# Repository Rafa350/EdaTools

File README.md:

# EdaTools

Tools and utilities for PCB design.
!!!Very early version. Runs ok for my works.

## EdaImport
* Convert EAGLE v7 BRD file to EdaTools board file (.XBRD)
* Convert EAGLE v7 LBR file to EdaTools library file (.XLIB)
* Convert KiCad pcb file to EdaTools board file (.XBRD)

## EdaExport
* Convert EdaTools board file (.XBRD) to EAGLE or KiCAD
* Convert EdaTools library file (.XLIB) to KiCAD footprint library

## EdaExtractor.
* Extract information from board (BOM, Centroids, etc)

## EdaPanelizer.
* Merge any number of boards to create a single board panel.

## EdaCAMTool.
* Create production files from CAM project file (.XCAM).
* Generate gerber X3 image files.
* Generate gerber X3 drill and route files.
* Generate IPC-D356 file.
* Generate IPC-2581C file.
* Compliant with Ucamco Gerber File Format Specification (www.ucamco.com).
* Passed Gerber test with "https://gerber-viewer.ucamco.com/".
* Passed IPC2581C test with 3D PCBA Viewer.

## Notes.
* I used this tool for convert KiCAD to IPC2581 for board fabrication. Pending for assembly.

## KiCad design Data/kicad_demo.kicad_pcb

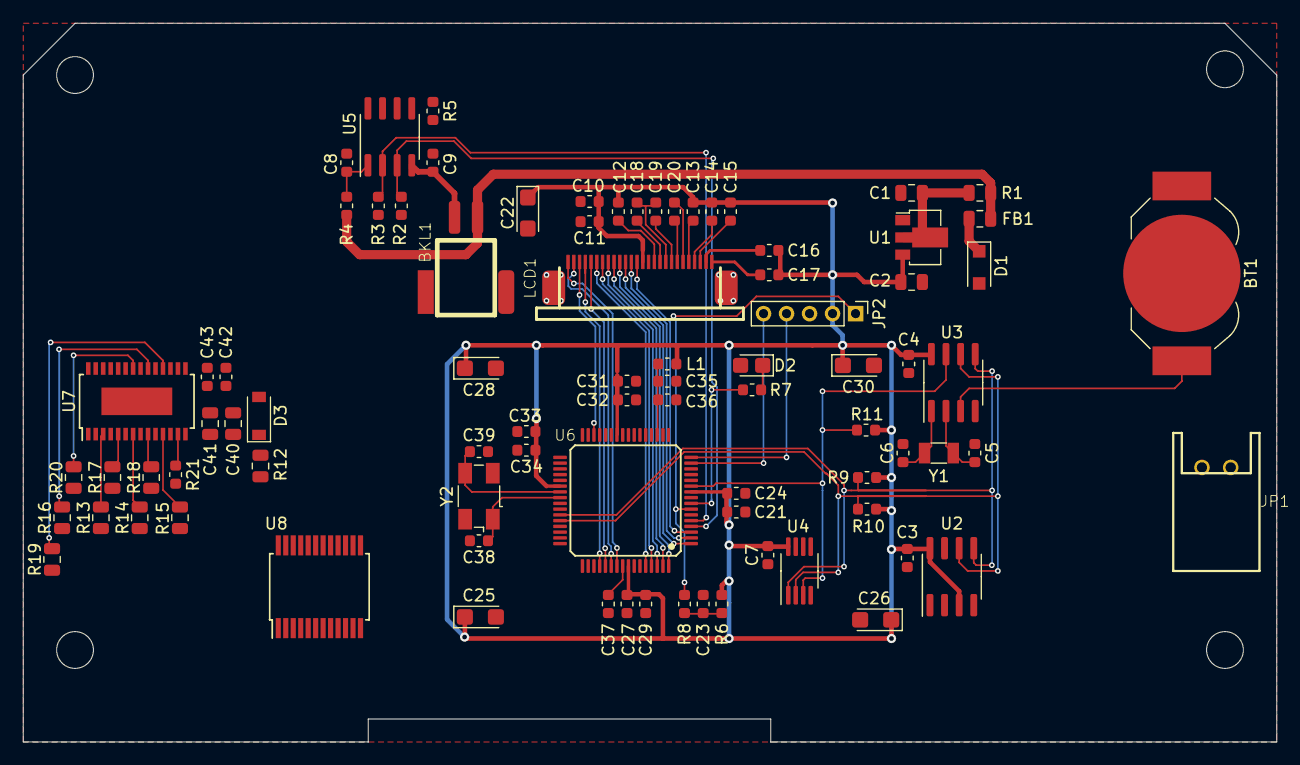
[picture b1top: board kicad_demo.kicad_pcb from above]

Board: 2 copper layers, 109.0 x 62.5 mm, 84 parts (0 on the bottom side), 63 nets.

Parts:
BKL1: ERC12864-3-BK; ER-CON2.0-2P-SMD
BT1: Battery_Cell; BatteryHolder_LINX_BAT-HLD-012-SMT
C1, C2: 4u7; C_0805_2012Metric
C3, C4, C7, C8, C10, C23, C24, C29, C32, C34, C36, C42: 100n; C_0603_1608Metric
C5, C6: 14p; C_0603_1608Metric
C9: 470n; C_0603_1608Metric
C11: 10u; C_0603_1608Metric
C12, C13, C14, C15, C16, C17, C18, C19, C20: 1u; C_0603_1608Metric
C21, C27, C31, C33, C35, C37: 10n; C_0603_1608Metric
C22, C25, C26, C28, C30: 10u; CP_EIA-3216-18_Kemet-A
C38, C39: 22p; C_0603_1608Metric
C40: 10u; C_0805_2012Metric
C41: 100n; C_0805_2012Metric
C43: 4u7; C_0603_1608Metric
D1: MBR0540; D_SOD-123F
D2: HSMG-C170; LED_0805_2012Metric_Castellated
D3: MMSZ5258BT1G; D_SOD-123
FB1: 600R; L_0805_2012Metric
JP1: S02B-XASK-1
JP2: PINHD-1X5-2MM; PinHeader_1x05_P2.00mm_Vertical
L1: 600R; L_0603_1608Metric
LCD1: ERC12864-3; ER-CON26HB-1
R1: 5R1; R_0805_2012Metric
R2, R3: 100K; R_0603_1608Metric
R4: 100R; R_0603_1608Metric
R5: 1K66; R_0603_1608Metric
R6, R11: 10K; R_0603_1608Metric
R7: 270; R_0603_1608Metric
R8: 1K; R_0603_1608Metric
R9, R10: 1K5; R_0603_1608Metric
R12: 150R; R_0805_2012Metric
R13, R14, R15, R16, R17, R18, R19, R20: 2K2; R_0805_2012Metric
R21: 15K; R_0603_1608Metric
U1: MCP1703A-3302_SOT89; SOT-89-3
U2: 24LC1025; SOIC-8_3.9x4.9mm_P1.27mm
U3: MCP7940N-xST; SOIC-8_3.9x4.9mm_P1.27mm
U4: MCP9804_MSOP; MSOP-8_3x3mm_P0.65mm
U5: STCS05; SOIC-8_3.9x4.9mm_P1.27mm
U6: PIC32MX4H_PT; TQFP64-10X10
U7: MAX31911; TSSOP-28-1EP_4.4x9.7mm_P0.65mm
U8: NCV7240; SSOP-24_5.3x8.2mm_P0.65mm
Y1: CM7V-T1A; Crystal_SMD_3215-2Pin_3.2x1.5mm
Y2: ABM3B; Crystal_SMD_Abracon_ABM3B-4Pin_5.0x3.2mm

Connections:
+3V3: C2.1, C3.1, C4.1, C7.1, C10.1, C11.1, C12.1, C13.1, C14.1, C15.1, C16.1, C17.1, C21.1, C22.1, C24.1, C25.1, C26.1, C27.1, C28.1, C29.1, C30.1, C31.1, C32.1, C33.1, C34.1, JP2.2, L1.2, LCD1.14, R6.1, R9.1, R10.1, R11.2, U1.3, U2.3, U2.8, U3.8, U4.8, U6.10, U6.26, U6.38, U6.57
+5V: BKL1.1, FB1.1, R1.2, R4.2
/CPU/LED: R7.1, U6.8
/CPU/MCLR: JP2.1, R8.2, U6.7
/CPU/PGEC1: JP2.5, U6.15
/CPU/PGED1: JP2.4, U6.16
ALERT: R11.1, U3.7, U4.3, U6.11
BK-EN: R2.1, U5.3, U6.4
BK-PWM: R3.1, U5.2, U6.5
DSP-A0: LCD1.3, U6.30
DSP-CS: LCD1.1, U6.55
DSP-D0: LCD1.6, U6.60
DSP-D1: LCD1.7, U6.61
DSP-D2: LCD1.8, U6.62
DSP-D3: LCD1.9, U6.63
DSP-D4: LCD1.10, U6.64
DSP-D5: LCD1.11, U6.1
DSP-D6: LCD1.12, U6.2
DSP-D7: LCD1.13, U6.3
DSP-RD: LCD1.5, U6.53
DSP-RST: LCD1.2, U6.54
DSP-WR: LCD1.4, U6.52
GND: BT1.2, C1.2, C2.2, C3.2, C4.2, C5.2, C6.2, C7.2, C8.2, C9.2, C10.2, C11.2, C21.2, C22.2, C23.1, C24.2, C25.2, C26.2, C27.2, C28.2, C29.2, C30.2, C31.2, C32.2, C33.2, C34.2, C35.2, C36.2, C37.2, C38.2, C39.2, D2.2, JP1.2, JP2.3, LCD1.15, R2.2, R3.2, R5.2, U1.1, U2.1, U2.2, U2.4, U2.7, U3.4, U4.4, U4.5, U4.6, U4.7, U5.6, U6.9, U6.20, U6.25, U6.41, Y2.2, Y2.4
GND1: C40.2, C41.2, C42.2, C43.2, D3.2, R21.2, U7.4, U7.6, U7.8, U7.10, U7.12, U7.17, U7.19, U7.21, U7.26, U7.27, U7.291, U7.292, U7.293, U7.294, U7.295, U7.296, U7.297, U7.298, U8.1, U8.2, U8.11, U8.12, U8.14, U8.15, U8.16, U8.17, U8.18
unnamed: BKL1.2, C9.1, U5.4
unnamed: BT1.11, BT1.12, U3.3
unnamed: C1.1, R1.1, U1.2
unnamed: C5.1, U3.2, Y1.1
unnamed: C6.1, U3.1, Y1.2
unnamed: C8.1, R4.1, U5.1
unnamed: C12.2, LCD1.16
unnamed: C13.2, LCD1.22
unnamed: C14.2, LCD1.23
unnamed: C15.2, LCD1.24
unnamed: C16.2, LCD1.25
unnamed: C17.2, LCD1.26
unnamed: C18.1, C19.1, LCD1.18
unnamed: C18.2, LCD1.17
unnamed: C19.2, LCD1.19
unnamed: C20.1, LCD1.21
unnamed: C20.2, LCD1.20
unnamed: C23.2, R6.2, R8.1
unnamed: C35.1, C36.1, L1.1, U6.19
unnamed: C37.1, U6.56
unnamed: C38.1, U6.40, Y2.1
unnamed: C39.1, U6.39, Y2.3
unnamed: C40.1, C41.1, D3.1, R12.1, U7.14
unnamed: C42.1, C43.1, U7.1, U7.2, U7.15, U8.13, U8.21, U8.24
unnamed: D1.1, FB1.2
unnamed: D1.2, JP1.1
unnamed: D2.1, R7.2
unnamed: R5.1, U5.5
unnamed: R13.1, U7.3
unnamed: R14.1, U7.7
unnamed: R15.1, U7.11
unnamed: R16.1, U7.20
unnamed: R17.1, U7.5
unnamed: R18.1, U7.9
unnamed: R19.1, U7.18
unnamed: R20.1, U7.22
unnamed: R21.1, U7.13
SCL1: R10.2, U2.6, U3.6, U4.2, U6.44
SDA1: R9.2, U2.5, U3.5, U4.1, U6.43

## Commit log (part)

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2018-01-26 Dibuix correcte de poligons en pantalla. Dibuix correcta de rectangles i cercles plens o perfilats Proves amb fons Hershey
2018-01-27 Millores en el gerber per acostar-se al maxim a les especificacions de ucamco Afeigit el parametre BoardSide en la generacio dels poligons
2018-01-27 Renombrada la llibraria CAM Eina CAM per la generacio de gerbers
2018-01-29 Millores en la lectura i escriptura de la placa en un stream
2018-01-29 Commit final del dia
2018-01-31 Afeigit attributs en el bloc Lectura dles atributs al carregar la placa. Eliminada la propietat isolation en les regions. Optimitzacio del generador gerber.
2018-01-31 Revisio dels visitadors Optimitzacio de la generacio dels fitxers gerbers
2018-02-01 Afeigits el readme i la llivcencia per github
2018-02-02 Millores en la deteccio d'errors de parametres en el generador gerber. Modificat la funcio d'escriure atributs gerber. Canvis en noms incongruents.
2018-02-03 Millores en el generador de visuals. Un visual per capa. Cada visual de capa te visuals fills dels elements de la capa. D'aquesta manera es pot controlar la transparencia, el color i la visibilitat d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
2018-02-04 Clase Angle per representar tots els angles de rotacio, arcs, etc El gerber ya representa correctament la separacio del perfil en els poligons
2018-02-06 Modificacions en el visor de plaques
2018-02-07 Implementacio dels fonts heshey Afeigit clearance en les senyals
2018-02-08 Creacio del font standard
2018-02-19 Gestio de fonst vectorials
2018-02-20 Fonts vectorials
2018-02-21 Creacio de fonts. El element text te en compte la rotacio i posicio de l'atribut
2018-02-22 Mes fonts Ajust de l'orientacio dels texts, tant literals, com asignats a un atribut.
2018-02-26 Optimitzacio llistes de poligons
2018-02-27 Reorganitzacio del projecte EdaImport
2018-02-27 Aliniacio textes
2018-02-28 Atributs de Part. Posicio rotacio i aliniacio. Nova clase TextDrawer per dibuixar textes. Es por derivar per dibuixar en qualsevol dispositiu vectorial
2018-03-02 Gestio dels parasmetres dels parts
2018-03-04 Poligons i fonts implementats amb arrays. PolygonBuilder adaptat a arrays de punts. Restructuracio de la carpeta Geometry.
2018-03-06 Creacio de les clases PointInt, SizeInt, i RectInt GlyphPoint es substutuit per PointInt
2018-03-07 Canvi de geometria double a int
2018-03-09 Canvi a aritmetica amb enters
2018-03-10 Complert el traspas a geometria amb enters
2018-03-11 final del dia
2018-03-14 Nou: Generacio de fitxers IPCD365
2018-03-14 Correccio de bugs en el calcul de la corona en vias i pads Millores el la generacio IPCD365
2018-03-15 Nova clase SignalVisitor
2018-03-17 Corregit errors amb arcs de mes de 180 graus
2018-03-21 Fitxers XSL per conversio a fitxers de produccio
2018-03-22 Reorganitzacio del projecte. Nova llibreria EdaCommonLibrary
2018-03-26 Commit de seguretat
2018-04-08 Fix: Peta quant intenta visualitzar una capa inexistent
2018-04-15 Carrega els fonts de la carpeta relativa al executable. Batch de generacio dels fitxers de produccio. Ignora les carpetes els fitxers de produccio (Data/Production/*)
2018-07-20 Millores en la deteccio d'error del importador eagle
2018-07-24 Implementacio GetOutline per l'element regio.
2018-07-25 Millores en la generacio de gerber Correccio en el el generador xsl del bom per eurocircuits
2018-07-26 Arreglos en CircleElement, RectangleElement Reorganitzacio de XmlNodeHelper
2018-07-30 Opcio Filled en objectes rectangle, circle i RegionElement Visuals per cada tipus d'objecte Pbjecte cachePen i cacheBrush com entitats separades
2018-07-30 Visuals de cada element
2018-07-31 Restructuracio del visor de plaques Zoom i pan correctes
2018-07-31 Millores generals en EdaPCBViewer Calcul del tamany de la placa. Bounding box de les linies. Metodes utils en PointInt, SizeInt i RectInt
2018-08-02 Arreglos cosmetics
2018-08-02 Optimitzacio zoom i pan en EdaPCBViewer
2018-08-06 Gnenerador CAM per fitxers DXS del perfil de la placa
2018-08-07 VisualDrawer optimitzat e independitzat de la resta.
2018-08-10 Nou lector de plaques. Gestio dels pads en els blocs millorada. Creacio retardade de les llistes d'atributs i pads
2018-08-12 Restructuracio Geometry Millores en la importacio Eagle Optimitzacio en XmlBoardReader i XmlBoardWriter Arreglos cosmetics generals
2018-08-13 Restructuracio dels fitxers i carpetes. Clases XmlWriterAdapter i XmlReaderAdapter. Cleses helper per Xml en cada tipus que ho necesiti. Mes lletres en els fonmts Nova clase DistanceUnits Nova clase 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
2018-08-27 Generacio de fitxers CAM per panells multiplaca
2018-08-28 Restructuracio del model
2018-08-29 Panelitzacio en la sortida gerber Lecturs de panells XPNL
2018-08-30 Generador CAM per ipc-d356 per panell
2018-09-07 Restructuracio de la gestio de capes. Cada element de la placa te el seu LayerSet on constant en quines capes el renderitzen. Si la placa en la que esta te una capa del LayerSet, la dibuixa, si no, c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
2018-09-07 Restructuracio general. Funcio Clone en elements de placa. Funcions d'extensio en XmlReaderAdapter pels tipus basics (Point, Size, Angle, etc
2018-09-08 Millores en el panelitzador. Gestio de les capes amb LayerId, i LayerSet Gestio de la capa outlineLayer
2018-09-09 Millores en el panelitzador. Revisio Block canvi de HashSet per List
2018-09-10 Implementacio amb noves col·leccions
2018-09-10 Proves amb WriteableBitmap
2018-09-11 Restructuracio dels fitxers board
2018-09-11 Millores en les coleccions per evitar memory leaks
2018-09-12 Revisio coleccions
2018-09-15 Restructuracio del render WPF
2018-09-16 Caper visuals (En estudi)
2018-09-19 Restructuracio en lectura i escriptura de fitxers XBRD
2018-09-20 Restructuracio
2018-09-27 Optimitzacione en el renderitzat
2018-10-20 Cambis cosmetics
2018-11-01 Millores en la carrega del projecte XCAM
2018-11-02 Millores en el generador CAM
2018-11-06 Millores en el procesador CAM
2018-11-16 Millores en la lectura dels fitxers de placa
2018-11-16 Corregit: No troba el schema per la lectura del fitxer XPNL
2018-11-19 Millores en la lectura de fitxers XPNL, XBRD i XCAM Hole nomes en la capa Hole, implicitament afecta a totes. Lectura de posicio i rotacio en projectes CAM
2018-11-21 Canvis en el format del fitxer xpnl
2018-11-23 Nou projecte EdaHDCLibrary
2018-11-25 Compilador HDL
2018-11-27 Millores en el parser HDL
2018-11-28 Gramatica pel HDL
2018-11-29 Parser PHDL completat Objectes AST complert
2018-11-29 Afeigit TODO
2018-11-30 Restructuracio de EdaPCBLibrary
2018-12-01 Restructuracio del model. Simplicifacio de les coleccions.
2018-12-02 Restructuracio i simplificacio
2018-12-04 Millores en el panelitzador
2018-12-04 Panelitzador
2018-12-06 Millores en el panelitzador.
2018-12-08 Correccio error greu en LayerSet.Parse que impedia la identificacio corerecte de les capes Correccio en la posicio del forats en els fitxers gerber
2018-12-09 Millores en el parser de LayerId
2018-12-10 Restructuracio en la llibraria EdaCAM
2018-12-11 Parametres d'entrada al panelitzador. Millores en el build
2018-12-13 Restructuracio i millores en l'editor de panells
2018-12-15 Restructuracio dels visitadors
2018-12-17 Restructuracio de BoardEditor Objectes visuals per BoardEditor
2018-12-21 Restructuracio dels editors Nou ensamblat per grafics wpf
2018-12-21 Mapa de conectivitat inici de la implementacio
2018-12-22 Restructuracio del editor de panells Simplificacio del renderitzat
2018-12-31 Canvi del format dels fitxert xpnl Correccio d'errors en el panelitzador i en el editor de panells
2018-12-31 Actualitzacio projecte doxygen
2019-01-05 Correccio del renderitzat de poligons en parts situats en la capa inferior
2019-01-07 Millores en VisualLayer
2019-01-09 Millores en EdaPanelizer Correccio d'errors en Setup
2019-01-09 Canvi en la forma d'identificar si un part esta voltejat Objecte IStreamLocator, per localitzar streams en els projectes
2019-01-11 Remodelacio de les capes Importar Eagle
2019-01-13 Restructuracio EdaCAMTool
2019-01-17 Restructuracio EdaPanelizer y EdaCamTool
2019-01-18 Perfil de les plaques en el editor de panells
2019-01-23 Canvis en la llista d'ignorats
2019-01-24 Millores en EdaPanelizer i en EdaPanelEditor
2019-01-26 Elimina la clase Color per innecesaria
2019-02-01 Correccions en el panelitzador Millores en la visualitzacio del editor de panells
2019-02-02 Afeigida la gestio de llibreries de components
2019-02-04 Mes lletres en el font per defecte Correccio d'errors en el visual dels textos
2019-02-05 Proves amb netlist
2019-02-07 Correccions al importar el netlist desde eagle
2019-02-08 Canvis en el sistema de renderitzat en PanelEditor
2019-02-10 Restructuracio en DesignTool
2019-02-12 Eliminacio de Angle en DesignTool
2019-02-16 Correccions en EdaPanelEditor
2019-02-18 Canvis cosmetics
2019-02-19 Restructuracio i millores en RulerBox
2019-02-22 Millores en ContentBox
2019-02-28 Canvis en les eines de dibuix.
2019-03-30 Verificacio de capes duplicades en AddLayer
2019-04-07 Millores al importar Eagle Preparacio por importar KiCad
2019-04-27 Canvis en els ViewModel
2019-06-19 Canvis en Rect i en Size
2019-08-27 Optimitzacio i millores en WindowState
2019-12-31 Restructuracio general per identificar versions
2020-01-03 Afeigit carpeta d'exemles i proves
2020-01-04 Canvi a nova versio v2.0. -NET Core v3.1
2020-01-04 Correccions en les propietats dels paquets.
2020-01-10 Millores en matrius 2D. Obtingut de AvaloniaUI
2020-01-10 interface Equatable<> en Point, Angle, etc. Nova clase Corners.
2020-01-12 Control RulerBox
2020-01-14 Millores en la regla
2020-02-24 Milleres en el controls de diseny
2020-02-25 Millores en renderitzar dels controls de diseny
2020-03-04 Intent de crear un editor grafic generic Nou SceneControl per mostrasr escenes.
2020-03-08 Cache de poligons. Llista de punts inmutable. Eines de dibuix. Restructuracio SceneView.
2020-05-20 Canvis en la llicencia
2020-05-28 Restructuracio carpetes
2020-06-27 Millores en el importador Kicad
2020-06-28 Millores importacio KiCad
2020-07-02 Revisions cosmetiques
2021-05-03 Importacio i exportacio Kicad
2021-05-04 Importacio kicad
2021-05-08 Correccions en l'aliniacio de textos. Correccions en la substitucio de macros {} Correccions en la importacio KiCad
2021-05-08 Compressio de la versio antiga
2021-05-11 bug: IPCD356 vies sense senyal asignada provocan excepcio: resolt
2021-05-12 Nova aplicacio EdaCOmpònentGenerator
2021-05-19 Correccio bug en el renderitzat dels poligons. Revisio en la importacio KiCad
2021-05-22 Rediseny de capes i identificador de capes
2021-05-28 Extensio per la clase Component Unificacio esquemes XBRD i XLIB Revisio Doxygen
2021-06-07 Revisio IVisitable Actualitzacio Avalonia
2021-12-14 Generacio del fitxer Gerber-JOB
2021-12-15 Millorres en gerber-job
2021-12-19 Revisio ThPad i SmdPad clase EdaPoints
2021-12-24 Revisio EagleImport
2021-12-27 Importar KiCad 6
2022-01-17 Importa propietats de la placa Kicad
2022-01-23 Millores en Gerber drill/route Eliminacio del element Hole
2022-02-06 Millores en la compatibilitat KiCad 6
2022-02-07 Millores en la generacio gerber Millores en la importacio KiCad i Eagle Pads i slots
2022-02-13 Millora importacio arcs KiCad
2022-06-15 Revisio d'errors en la exportacio a KiCad 6
2022-10-09 Revisio generasls dels poligons. Canvi a versio 2 de clipper.
2022-10-12 Revisio regions, thermals, etc
2022-10-12 Filled en Circle, Rectangle i Polygon
2022-10-13 Revisio poligons
2022-10-14 Resisio importador KiCad
2022-10-16 Utilitza alia pels noms de senyals en el fitxer IPC-356-A
2022-10-17 Nova llibraria EddaCoreExtensions Millores en la exportacio IPC2581
2022-10-19 Revisio IPC2581Generator
2022-10-20 Revisio IPC2581
2022-10-23 Comit
2022-10-24 Revisio IPC2581, versio preliminar utilitzable
2022-10-24 Asignacio de nom segur a tots els projectes
2022-10-26 Revisio de la gestio del senyals
2022-10-30 Afeigit silkscreen en el fitxer IPC2582
2022-10-31 Cache de poligons per m,illorar la velocitat de renderitzat. Redistribucio dels espai de noms IO
2022-11-01 Revisio cercles en LayerFeatures en IPC-2581 Importacio de cercvles en Kicad Revisio EdaBoardViewer
2022-11-02 EdaLineBaseElement com a base abstracta per linies i arcs
2022-11-19 Correccio offsets amb Clipper2
2022-12-17 Revisio IPC2581 Tots els angles (EdaAngle) son sempre normalitzats.
2022-12-18 Revisio errors en la importacio del plaques KiCad
